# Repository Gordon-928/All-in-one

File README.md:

# All-in-one
Design and program of a small package data collection device
This project aims to learn the bascis of using STM32 MCU and PCB layout with MCU and sensors. The ultimate goal of the project is to develope a all-in-one sensor to collect flight data of a rocket, drop tests and other possible usage. Personal goal is to make a sensor close to commercial grade with all well-thought start-up sequence, easy to use and robust software.

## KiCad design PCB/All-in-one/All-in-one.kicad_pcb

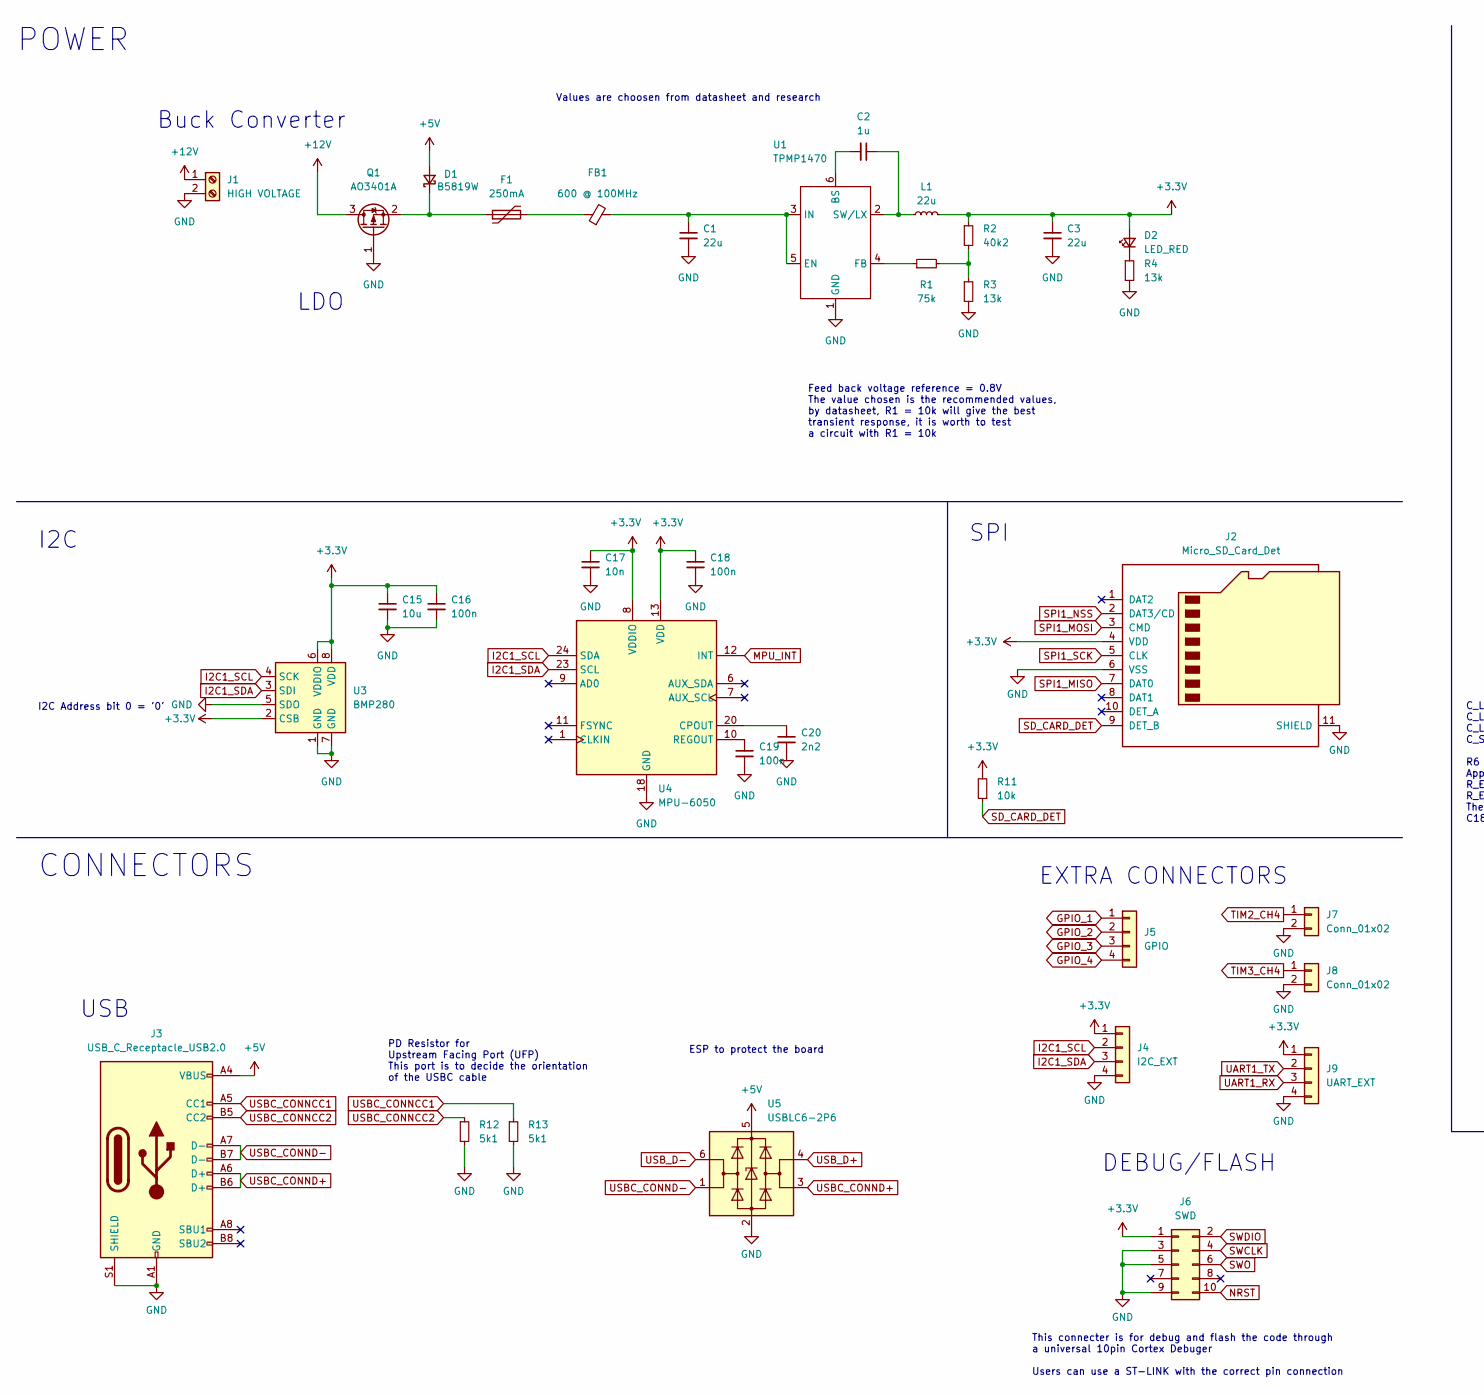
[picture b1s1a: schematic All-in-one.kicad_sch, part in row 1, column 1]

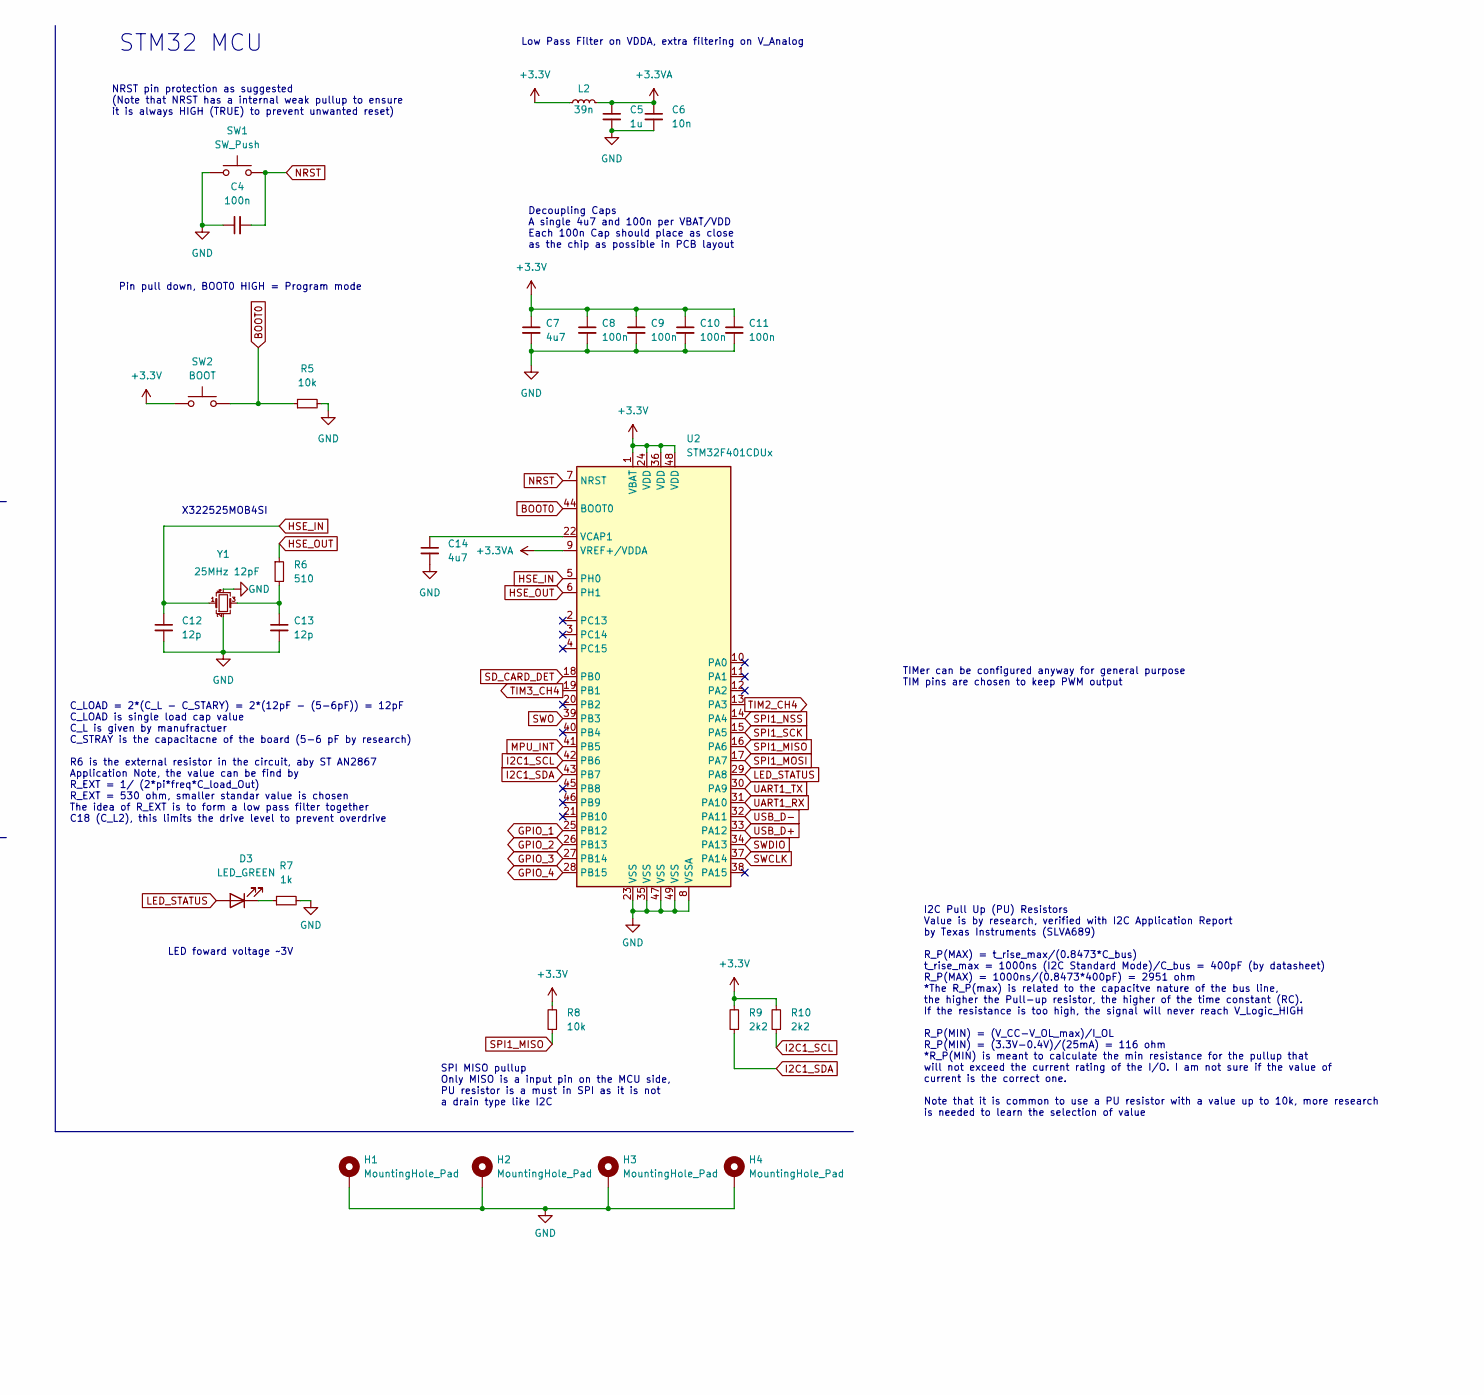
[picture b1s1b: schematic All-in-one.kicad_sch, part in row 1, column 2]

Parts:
C1, C3: 22u; C_1206_3216Metric; LCSC C12891
C2: 1u; C_0805_2012Metric; LCSC C2798196
C4, C8, C9, C10, C11, C16, C18, C19: 100n; C_0402_1005Metric; JLCPCB Part# C307331
C5: 1u; C_0603_1608Metric; JLCPCB Part# C15849
C6, C17: 10n; C_0402_1005Metric; JLCPCB Part# C15195
C7, C14: 4u7; C_0603_1608Metric; JLCPCB Part# C19666
C12, C13: 12p; C_0402_1005Metric; JLCPCB Part# C1547
C15: 10u; C_0603_1608Metric; JLCPCB Part# C96446
C20: 2n2; C_0402_1005Metric; JLCPCB Part# C1531
D1: B5819W; D_SOD-123; JLCPCB Part# C8598
D2: LED_RED; LED_0603_1608Metric; LCSC C965799
D3: LED_GREEN; LED_0603_1608Metric; JLCPCB Part# C87326
F1: 250mA; Fuse_1206_3216Metric; PART ID SMD1206B025TF/24; JLCPCB Part# C269113
FB1: 600 @ 100MHz; L_1206_3216Metric; JLCPCB Part# C73732
H1, H2, H3, H4: MountingHole_Pad; MountingHole_3.5mm_Pad_Via
J1: HIGH VOLTAGE; TerminalBlock_TE_282834-2_1x02_P2.54mm_Horizontal
J2: Micro_SD_Card_Det; SD_Card_custom
J3: USB_C_Receptacle_USB2.0; USB_C_16PIN
J4: I2C_EXT; PinHeader_1x04_P2.54mm_Vertical
J5: GPIO; PinHeader_1x04_P2.54mm_Vertical
J6: SWD; PinHeader_2x05_P2.54mm_Vertical
J7, J8: Conn_01x02; PinHeader_1x02_P2.54mm_Vertical
J9: UART_EXT; PinHeader_1x04_P2.54mm_Vertical
L1: 22u; MPIT8040; LCSC C281320
L2: 39n; L_0402_1005Metric; JLCPCB Part# C86063
Q1: AO3401A; SOT-23; JLCPCB Part# C15127
R1: 75k; R_0603_1608Metric; LCSC C18671
R2: 40k2; R_0603_1608Metric; LCSC C25893
R3, R4: 13k; R_0603_1608Metric; LCSC C2907101
R5, R8, R11: 10k; R_0402_1005Metric; JLCPCB Part# C25744
R6: 510; R_0402_1005Metric; JLCPCB Part# C25123
R7: 1k; R_0603_1608Metric; JLCPCB Part# C21190
R9, R10: 2k2; R_0603_1608Metric; JLCPCB Part# C4190
R12, R13: 5k1; R_0402_1005Metric; JLCPCB Part# C25905
SW1: SW_Push; GT-TC029; JLCPCB Part# C843669
SW2: BOOT; GT-TC029; JLCPCB Part# C843669
U1: TPMP1470; SOT-23-6; LCSC C558426
U2: STM32F401CDUx; QFN-48-1EP_7x7mm_P0.5mm_EP5.6x5.6mm
U3: BMP280; Bosch_LGA-8_2x2.5mm_P0.65mm_ClockwisePinNumbering
U4: MPU-6050; InvenSense_QFN-24_4x4mm_P0.5mm
U5: USBLC6-2P6; SOT-666; JLCPCB Part# C2827693
Y1: 25MHz 12pF; Crystal_SMD_3225-4Pin_3.2x2.5mm; PART ID X322525MOB4SI; JLCPCB Part# C9006

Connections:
+3.3V: C3.1, C7.1, C8.1, C9.1, C10.1, C11.1, C15.1, C16.1, C17.1, C18.1, D2.2 (A), J2.4 (VDD), J4.1, J6.1, J9.1, L1.2, L2.1, R2.1, R8.2, R9.2, R10.2, R11.2, SW2.1, U2.1 (VBAT), U2.24 (VDD), U2.36 (VDD), U2.48 (VDD), U3.2 (CSB), U3.6 (VDDIO), U3.8 (VDD), U4.8 (VDDIO), U4.13 (VDD)
+3.3VA: C5.1, C6.1, L2.2, U2.9 (VREF+/VDDA)
+5V: D1.2 (A), J3.A4 (VBUS), J3.A9 (VBUS), J3.B4 (VBUS), J3.B9 (VBUS), U5.5 (VBUS)
+12V: J1.1, Q1.3 (D)
BOOT0: R5.1, SW2.2, U2.44 (BOOT0)
GND: C1.2, C3.2, C4.1, C5.2, C6.2, C7.2, C8.2, C9.2, C10.2, C11.2, C12.2, C13.2, C14.2, C15.2, C16.2, C17.2, C18.2, C19.2, C20.2, H1.1, H2.1, H3.1, H4.1, J1.2, J2.6 (VSS), J2.11 (SHIELD), J3.A1 (GND), J3.A12 (GND), J3.B1 (GND), J3.B12 (GND), J3.S1 (SHIELD), J4.4, J6.3, J6.5, J6.9, J7.2, J8.2, J9.4, Q1.1 (G), R3.2, R4.2, R5.2, R7.2, R12.2, R13.2, SW1.1, U1.1 (GND), U2.8 (VSSA), U2.23 (VSS), U2.35 (VSS), U2.47 (VSS), U2.49 (VSS), U3.1 (GND), U3.5 (SDO), U3.7 (GND), U4.18 (GND), U5.2 (GND), Y1.2, Y1.4
GPIO_1: J5.1, U2.25 (PB12)
GPIO_2: J5.2, U2.26 (PB13)
GPIO_3: J5.3, U2.27 (PB14)
GPIO_4: J5.4, U2.28 (PB15)
HSE_IN: C12.1, U2.5 (PH0), Y1.1
HSE_OUT: R6.1, U2.6 (PH1)
I2C1_SCL: J4.2, R10.1, U2.42 (PB6), U3.4 (SCK), U4.24 (SDA)
I2C1_SDA: J4.3, R9.1, U2.43 (PB7), U3.3 (SDI), U4.23 (SCL)
LED_STATUS: D3.2 (A), U2.29 (PA8)
MPU_INT: U2.41 (PB5), U4.12 (INT)
NRST: C4.2, J6.10, SW1.2, U2.7 (NRST)
unnamed: C1.1, FB1.2, U1.3 (IN), U1.5 (EN)
unnamed: C2.1, L1.1, U1.2 (SW/LX)
unnamed: C2.2, U1.6 (BS)
unnamed: C13.1, R6.2, Y1.3
unnamed: C14.1, U2.22 (VCAP1)
unnamed: C19.1, U4.10 (REGOUT)
unnamed: C20.1, U4.20 (CPOUT)
unnamed: D1.1 (K), F1.1, Q1.2 (S)
unnamed: D2.1 (K), R4.1
unnamed: D3.1 (K), R7.1
unnamed: F1.2, FB1.1
unnamed: R1.1, U1.4 (FB)
unnamed: R1.2, R2.2, R3.1
SD_CARD_DET: J2.9 (DET_B), R11.1, U2.18 (PB0)
SPI1_MISO: J2.7 (DAT0), R8.1, U2.16 (PA6)
SPI1_MOSI: J2.3 (CMD), U2.17 (PA7)
SPI1_NSS: J2.2 (DAT3/CD), U2.14 (PA4)
SPI1_SCK: J2.5 (CLK), U2.15 (PA5)
SWCLK: J6.4, U2.37 (PA14)
SWDIO: J6.2, U2.34 (PA13)
SWO: J6.6, U2.39 (PB3)
TIM2_CH4: J7.1, U2.13 (PA3)
TIM3_CH4: J8.1, U2.19 (PB1)
UART2_RX: J9.3, U2.31 (PA10)
UART2_TX: J9.2, U2.30 (PA9)
USBC_CONNCC1: J3.A5 (CC1), R13.1
USBC_CONNCC2: J3.B5 (CC2), R12.1
USBC_CONND+: J3.A6 (D+), J3.B6 (D+), U5.3 (I/O2)
USBC_CONND-: J3.A7 (D-), J3.B7 (D-), U5.1 (I/O1)
USB_D+: U2.33 (PA12), U5.4 (I/O2)
USB_D-: U2.32 (PA11), U5.6 (I/O1)

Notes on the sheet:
TIMer can be configured anyway for general purpose TIM pins are chosen to keep PWM output
Buck Converter
PD Resistor for Upstream Facing Port (UFP) This port is to decide the orientation of the USBC cable
SPI
This connecter is for debug and flash the code through a universal 10pin Cortex Debuger Users can use a ST-LINK with the correct pin connection
DEBUG/FLASH
I2C Address bit 0 = '0'
I2C Pull Up (PU) Resistors Value is by research, verified with I2C Application Report by Texas Instruments (SLVA689) R_P(MAX) = t_rise_max/(0.8473*C_bus) t_rise_max = 1000ns (I2C Standard Mode)/C_bus = 400pF (by datasheet) R_P(MAX) = 1000ns/(0.8473*400pF) = 2951 ohm *The R_P(max) is related to the 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
EXTRA CONNECTORS
Feed back voltage reference = 0.8V The value chosen is the recommended values, by datasheet, R1 = 10k will give the best transient response, it is worth to test a circuit with R1 = 10k
Values are choosen from datasheet and research
SPI MISO pullup Only MISO is a input pin on the MCU side, PU resistor is a must in SPI as it is not a drain type like I2C
LED foward voltage ~3V
STM32 MCU
X322525MOB4SI
ESP to protect the board
I2C
POWER
Low Pass Filter on VDDA, extra filtering on V_Analog
C_LOAD = 2*(C_L - C_STARY) = 2*(12pF - (5-6pF)) = 12pF C_LOAD is single load cap value C_L is given by manufractuer C_STRAY is the capacitacne of the board (5-6 pF by research) R6 is the external resistor in the circuit, aby ST AN2867 Application Note, the value can be find by R_EXT = 1/ (2*pi*freq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
USB
Decoupling Caps A single 4u7 and 100n per VBAT/VDD Each 100n Cap should place as close as the chip as possible in PCB layout
LDO
CONNECTORS
Pin pull down, BOOT0 HIGH = Program mode
NRST pin protection as suggested (Note that NRST has a internal weak pullup to ensure it is always HIGH (TRUE) to prevent unwanted reset)

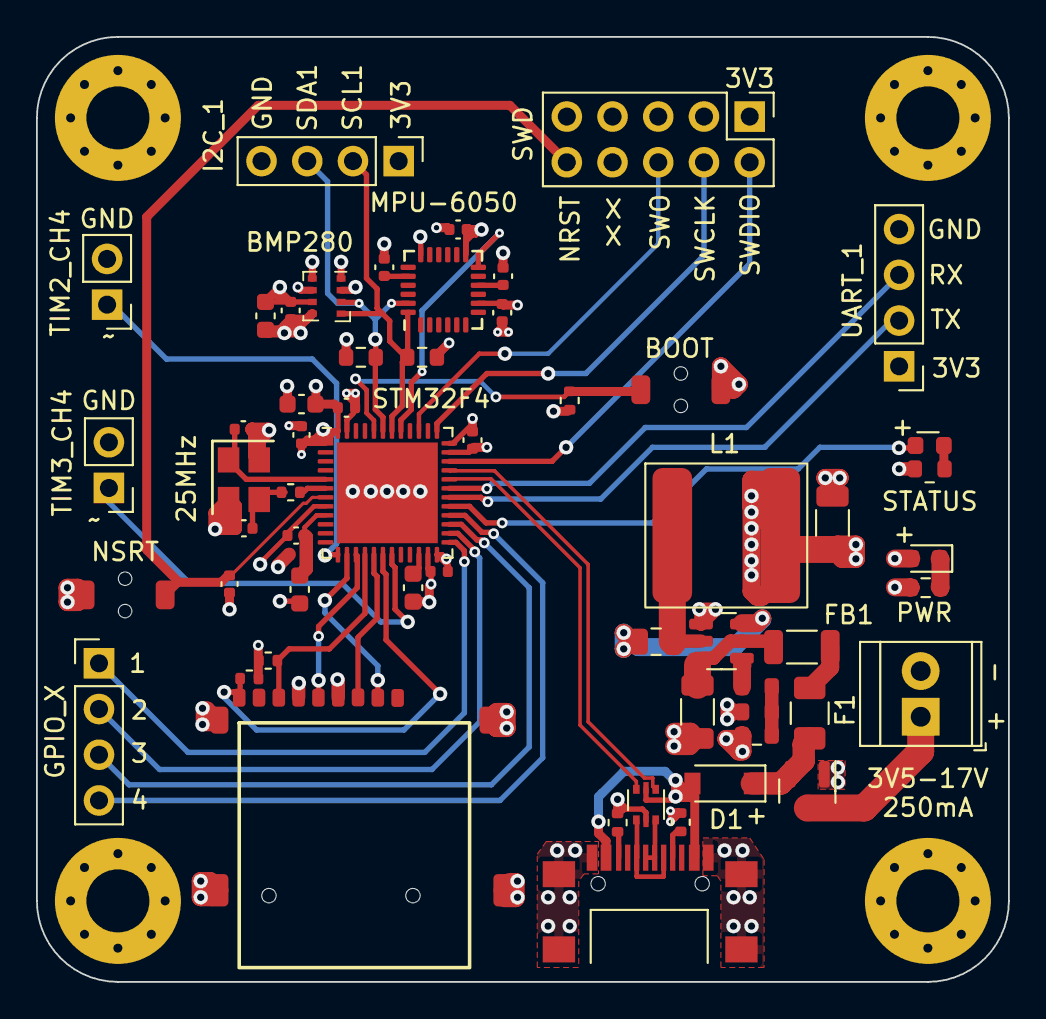
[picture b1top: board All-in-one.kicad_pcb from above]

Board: 4 copper layers, 54.0 x 52.5 mm, 62 parts (0 on the bottom side), 48 nets.

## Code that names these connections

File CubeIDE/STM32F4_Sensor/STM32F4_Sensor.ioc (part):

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Mcu.Name=STM32F401C(D-E)Ux
Mcu.Package=UFQFPN48
Mcu.UserName=STM32F401CDUx
PA10.Mode=OTG/Dual_Role_Device
PA10.Signal=USB_OTG_FS_ID
PA11.Mode=OTG/Dual_Role_Device
PA11.Signal=USB_OTG_FS_DM
PA12.Mode=OTG/Dual_Role_Device
PA12.Signal=USB_OTG_FS_DP
PA13.Mode=Trace_Asynchronous_SW
PA13.Signal=SYS_JTMS-SWDIO
PA14.Mode=Trace_Asynchronous_SW
PA14.Signal=SYS_JTCK-SWCLK
PA3.Signal=S_TIM2_CH4
PA4.Mode=NSS_Signal_Hard_Output
PA4.Signal=SPI1_NSS
PA5.Mode=Full_Duplex_Master
PA5.Signal=SPI1_SCK
PA6.Mode=Full_Duplex_Master
PA6.Signal=SPI1_MISO
PA7.Mode=Full_Duplex_Master
PA7.Signal=SPI1_MOSI
PA8.GPIOParameters=GPIO_Label
PA8.GPIO_Label=LED_STATUS
PA8.Signal=GPIO_Output
PA9.Mode=Asynchronous
PA9.Signal=USART1_TX
PB0.Signal=GPIO_Input
PB1.Signal=S_TIM3_CH4
PB12.GPIOParameters=GPIO_Label
PB12.GPIO_Label=GPIO_1
PB12.Signal=GPIO_Output
PB13.Signal=GPIO_Output
PB14.GPIOParameters=GPIO_Label
PB14.GPIO_Label=GPIO_3
PB14.Signal=GPIO_Output
PB15.GPIOParameters=GPIO_Label
PB15.GPIO_Label=GPIO_4
PB15.Signal=GPIO_Output
PB3.Mode=Trace_Asynchronous_SW
PB3.Signal=SYS_JTDO-SWO
PB5.GPIOParameters=GPIO_Label
PB5.GPIO_Label=MPU_INT
PB5.Signal=GPIO_Input
PB6.Mode=I2C
PB6.Signal=I2C1_SCL
PB7.Mode=Asynchronous
PB7.Signal=USART1_RX
PB9.Mode=I2C
PB9.Signal=I2C1_SDA
PH0\ -\ OSC_IN.Mode=HSE-External-Oscillator
PH0\ -\ OSC_IN.Signal=RCC_OSC_IN
PH1\ -\ OSC_OUT.Mode=HSE-External-Oscillator
PH1\ -\ OSC_OUT.Signal=RCC_OSC_OUT
RCC.HSE_VALUE=25000000
RCC.SYSCLKFreq_VALUE=84000000
RCC.SYSCLKSource=RCC_SYSCLKSOURCE_PLLCLK
board=custom

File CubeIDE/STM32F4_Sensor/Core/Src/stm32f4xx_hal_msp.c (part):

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
    __HAL_RCC_GPIOB_CLK_ENABLE();
    /**I2C1 GPIO Configuration
    PB6     ------> I2C1_SCL
    PB9     ------> I2C1_SDA
    */
    GPIO_InitStruct.Pin = GPIO_PIN_6|GPIO_PIN_9;
    GPIO_InitStruct.Mode = GPIO_MODE_AF_OD;
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    __HAL_RCC_I2C1_CLK_DISABLE();

    /**I2C1 GPIO Configuration
    PB6     ------> I2C1_SCL
    PB9     ------> I2C1_SDA
    */
    HAL_GPIO_DeInit(GPIOB, GPIO_PIN_6);

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
    __HAL_RCC_GPIOA_CLK_ENABLE();
    /**SPI1 GPIO Configuration
    PA4     ------> SPI1_NSS
    PA5     ------> SPI1_SCK
    PA6     ------> SPI1_MISO
    PA7     ------> SPI1_MOSI
    */
    GPIO_InitStruct.Pin = GPIO_PIN_4|GPIO_PIN_5|GPIO_PIN_6|GPIO_PIN_7;
    GPIO_InitStruct.Mode = GPIO_MODE_AF_PP;
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    __HAL_RCC_SPI1_CLK_DISABLE();

    /**SPI1 GPIO Configuration
    PA4     ------> SPI1_NSS
    PA5     ------> SPI1_SCK
    PA6     ------> SPI1_MISO
    PA7     ------> SPI1_MOSI
    */
    HAL_GPIO_DeInit(GPIOA, GPIO_PIN_4|GPIO_PIN_5|GPIO_PIN_6|GPIO_PIN_7);

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  /* USER CODE END TIM2_MspPostInit 0 */
    __HAL_RCC_GPIOA_CLK_ENABLE();
    /**TIM2 GPIO Configuration
    PA3     ------> TIM2_CH4
    */
    GPIO_InitStruct.Pin = GPIO_PIN_3;
    GPIO_InitStruct.Mode = GPIO_MODE_AF_PP;
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
    __HAL_RCC_GPIOB_CLK_ENABLE();
    /**TIM3 GPIO Configuration
    PB1     ------> TIM3_CH4
    */
    GPIO_InitStruct.Pin = GPIO_PIN_1;
    GPIO_InitStruct.Mode = GPIO_MODE_AF_PP;
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    __HAL_RCC_GPIOA_CLK_ENABLE();
    __HAL_RCC_GPIOB_CLK_ENABLE();
    /**USART1 GPIO Configuration
    PA9     ------> USART1_TX
    PB7     ------> USART1_RX
    */
    GPIO_InitStruct.Pin = GPIO_PIN_9;
    GPIO_InitStruct.Mode = GPIO_MODE_AF_PP;
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    __HAL_RCC_USART1_CLK_DISABLE();

    /**USART1 GPIO Configuration
    PA9     ------> USART1_TX
    PB7     ------> USART1_RX
    */
    HAL_GPIO_DeInit(GPIOA, GPIO_PIN_9);

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
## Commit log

2022-08-15 Project Initialization
    - Initialize KiCAD project
    - Uploaded datasheets
2022-08-28 Added draft schematic and STM32CubeIDE Project - Added all datasheets
    - Started schematic draftin
    - Started STM32C
2022-08-28 Push All Project Files to Repo - All files include STM32CubeIDE project files, untracked documents
2022-08-30 Draft Schematic - Schematic is 80%ish done, details on minor connections need more research - Wired sensors - Added extra connectors - SD card slot is NOT wired
2022-08-30 Minor Update
2022-08-31 Pin Finalize and Added SD Card Slot Via SPI - Pin and circuit are ready to final check - Added LDO for Lipo, a power source switch should be added
2022-09-02 REV X01 Schematic Completed - Schematic is completed, with the purpose of X01 being the proto board - External resistor of the external clock is left as a pad only, it is a bit unclear that if a exte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
2022-09-02 Updated Schematic and Footprint Assignments
    - Updated power supply circuit switch
    - Added custom foot prints
    - Assigned most of the footprints
2022-09-05 Updated PCB Layout
2022-09-09 Recovery File
2022-09-09 Completed PCB Layout (No Tracing) - Made PCB layout - Tracing need to be done
2022-09-11 Ver X01 PCB Routing Completed - PCB is completed and all MFG files are exported - gbr files are uploaded to JLCPCB for quoting - All parts needed to be sourced - Encounterd some bug at using CubeIDE
2022-09-12 Production Files Updated - Sent to JLCPCB for manufracturing - No SMD parts can be shipped with the order, to reduce the cost, it is most likely that a pre-assembled PCB will be ordered
2022-09-13 git add -A all missing files
2022-09-14 Updated Circuit - Based on the new parts supplier LCSC, better components can be found - PCB is updated according to the new components
2022-09-15 PCB Tracing Update - Reroute traces
2022-09-17 PCB Update - PCB is good to go - Order is on hold as there maybe other projects that requires ordering
2022-09-18 VER X01 Final Production Files - As the PCB is ordered, X01 is completed and wait for testing - The PCB is MFG as is in this commit
2022-09-26 Added .gitignore
2022-10-02 Added KiCAD gitignore
2022-10-02 Reorganized CubeIDE Project Files
2022-10-03 Updated CubeIDE Code and Reviewed All-in-one X01 PCB - updated PCB labelling (UART_1 is mis-labelled as UART_2 on both .sch and PCB) - Tried STM32 programming with simple PWM code
2023-01-03 Added code with Arduino framework - added code with arduino framework for other project testing - added dimension for PCB mounting holes

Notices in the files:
CubeIDE/STM32F4_Sensor/Core/Src/stm32f4xx_hal_msp.c:
Copyright (c) 2022 STMicroelectronics.
All rights reserved.
This software is licensed under terms that can be found in the LICENSE file
